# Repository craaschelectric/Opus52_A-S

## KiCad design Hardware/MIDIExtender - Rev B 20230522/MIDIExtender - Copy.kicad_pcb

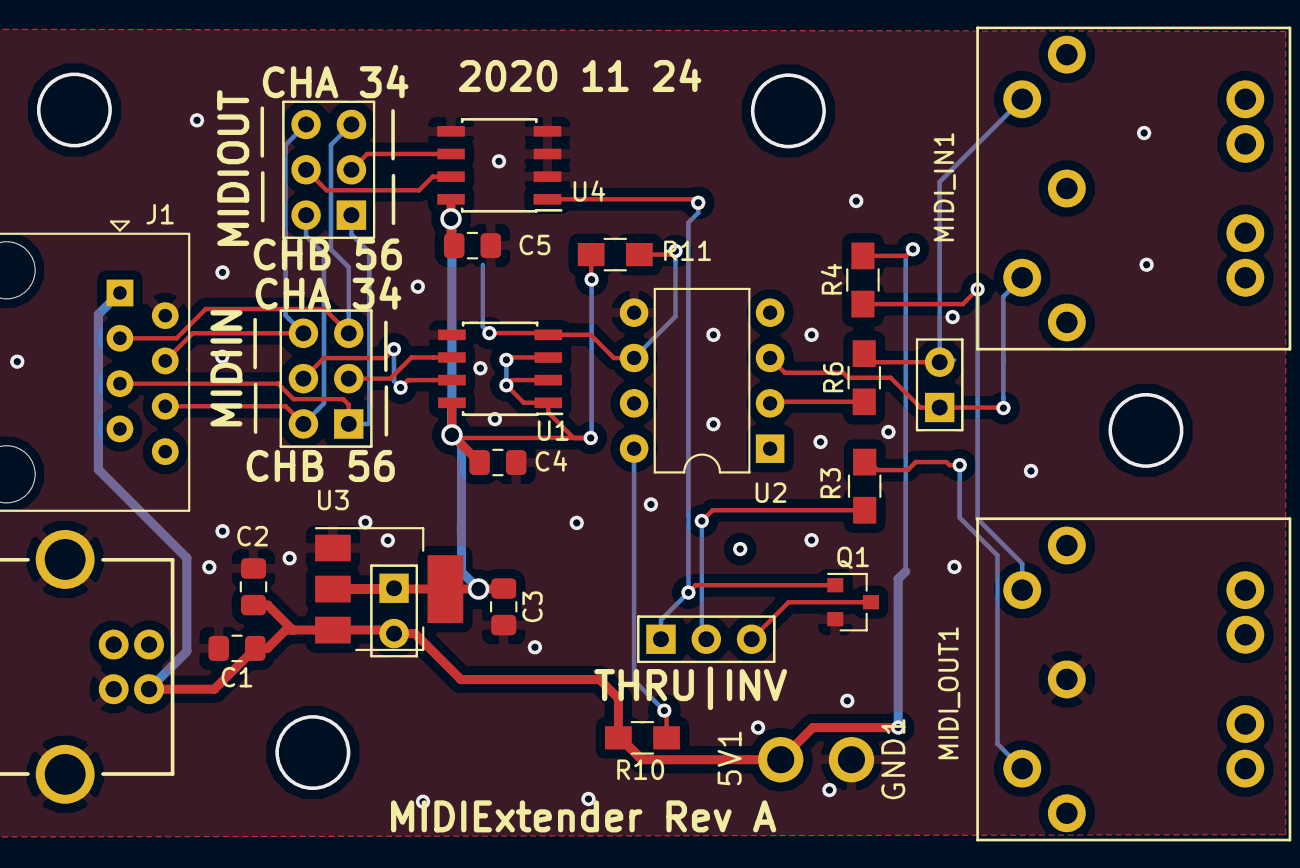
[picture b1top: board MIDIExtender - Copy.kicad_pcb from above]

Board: 2 copper layers, 26 parts (0 on the bottom side), 21 nets.

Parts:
5V1: Conn_01x01; KK156-1
C1, C2, C3, C4, C5: C; C_0805_2012Metric_Pad1.15x1.40mm_HandSolder
CHAN1, CHAN2: JBlock; H2X3-2.54
GND1: Conn_01x01; KK156-1
J1: RJ45; RJ45_Amphenol_54602-x08_Horizontal
J2, J10: Conn_01x02_Male; H2-2.54
JP1: DIP-USB-B-TYPE-FMAL_4+2P-2.0-90D_; USB4+2-2.5-90D-15.8X12MM
MIDI_IN1: DIN-5; DIN5_KCDX-5S-S2
MIDI_OUT1: DIN-5; DIN5_KCDX-5S-S2
Pol1: Conn_01x03; H3-2.54
Q1: 2N7002; SOT-23
R3, R4, R6, R11: 220; R_0805_HandSoldering
R10: 1K; R_0805_HandSoldering
U1, U4: ST485EBDR; SOIC-8_3.9x4.9mm_P1.27mm
U2: 6N138; DIP-8_W7.62mm
U3: AP1117-33; SOT-223-3_TabPin2

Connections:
/5V: 5V1.1, C1.1, C2.1, J1.1, J2.2, JP1.VBUS, R4.2, R10.2, U3.3
/MIDIIN: R11.1, U1.4, U2.6
GND: C1.2, C2.2, C3.2, C4.2, C5.2, GND1.1, J1.2, JP1.GND, JP1.S1, JP1.S2, MIDI_OUT1.3, Q1.2, U1.5, U2.5, U3.1, U4.2, U4.3, U4.4, U4.5
unnamed: C3.1, C4.1, C5.1, J2.1, R11.2, U1.1, U1.2, U1.3, U1.8, U3.2, U4.8
unnamed: CHAN1.1, CHAN2.1, J1.5
unnamed: CHAN1.2, U1.6
unnamed: CHAN1.3, CHAN2.3, J1.3
unnamed: CHAN1.4, CHAN2.4, J1.4
unnamed: CHAN1.5, U1.7
unnamed: CHAN1.6, CHAN2.6, J1.6
unnamed: CHAN2.2, U4.6
unnamed: CHAN2.5, U4.7
unnamed: J10.1, MIDI_IN1.4, U2.3
unnamed: J10.2, MIDI_IN1.2, R6.2
unnamed: MIDI_OUT1.2, R4.1
unnamed: MIDI_OUT1.4, R3.2
unnamed: Pol1.1, Q1.1, U4.1
unnamed: Pol1.2, R3.1
unnamed: Pol1.3, Q1.3
unnamed: R6.1, U2.2
unnamed: R10.1, U2.8

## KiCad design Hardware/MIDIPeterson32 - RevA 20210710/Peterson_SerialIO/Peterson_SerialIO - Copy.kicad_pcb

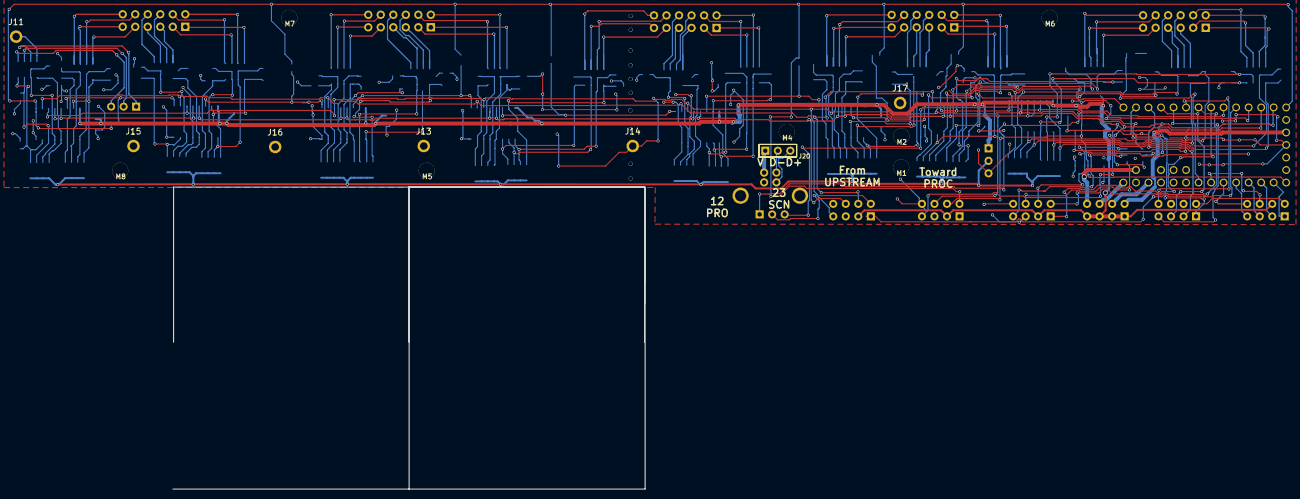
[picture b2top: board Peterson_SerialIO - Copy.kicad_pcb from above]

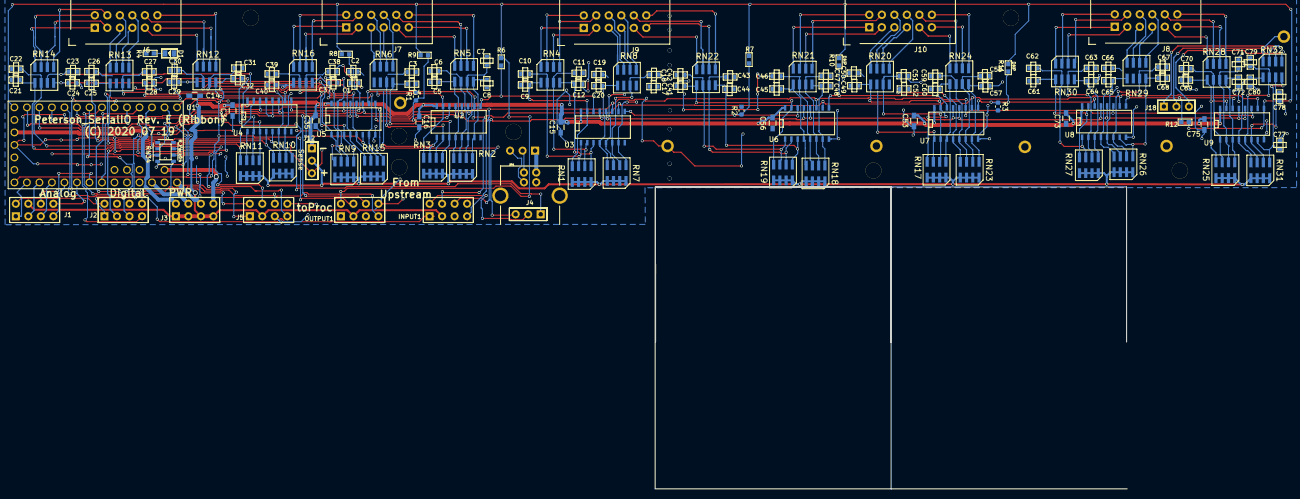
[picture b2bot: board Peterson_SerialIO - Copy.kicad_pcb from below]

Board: 2 copper layers, 156 parts (142 on the bottom side), 171 nets.

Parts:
C1, C2, C3, C4, C5, C6, C7, C8, C9, C10, C11, C12, C17, C18, C19, C20, C21, C22, C23, C24, C25, C26, C27, C28, C29, C30, C31, C32, C37, C38, C39, C40, C41, C42, C43, C44, C45, C46, C47, C48, C49, C50, C51, C52, C57, C58, C59, C60, C61, C62, C63, C64, C65, C66, C67, C68, C69, C70, C71, C72, C77, C78, C79, C80: 1nF or ESD; C0603
C14, C15, C16, C35, C36, C53, C56, C73, C75: C; R_0603_HandSoldering
D1: SMD-LED-CLEAR-GREEN_0805_; LED-0805
INPUT1: Conn_02x04_Counter_Clockwise; H2X4-2.54
J1, J2, J3, J5: Conn_02x04_Counter_Clockwise; H2X4-2.54
J4, J12, J18: Conn_01x03; H3-2.54
J6, J7, J8, J9, J10: Conn_01x12; RibbonCableSocket_12_OddEven
J11, J13, J14, J15, J16, J17: Conn_01x01; KK156-1
J20: Conn_01x03_Male; H3-2.54
JP1: DIP-USB-B-TYPE-FMAL_4+2P-2.0-90D_; USB4+2-2.5-90D-15.8X12MM
M1, M2, M4, M5, M6, M7, M8: Conn_01x01; Mounting#4
OUTPUT1: Conn_02x04_Counter_Clockwise; H2X4-2.54
R1, R2, R3: DNP; R_0603_1608Metric
R4: 1K; R0603
R6, R7, R8, R9, R10, R11, R12: DNP; R0603
RN1, RN2, RN3, RN4, RN5, RN6, RN7, RN8, RN9, RN10, RN11, RN12, RN13, RN14, RN15, RN16, RN17, RN18, RN19, RN20, RN21, RN22, RN23, RN24, RN25, RN26, RN27, RN28, RN29, RN30, RN31, RN32: R_Pack04; 2012-8
RN34: R_Pack04; RA2012-8
U1: Teensy3.2; Teensy3.x_LC
U2, U3, U4, U5, U6, U7, U8, U9: 74HC597; SO-16-N

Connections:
/ChainIn: J4.3, U1.9, U4.14
/EXT1PIN1: INPUT1.1, U1.10
/EXT1PIN8: J4.1, U1.11
/InRegLoad: INPUT1.6, OUTPUT1.6, RN34.8, U1.12, U2.12, U2.13, U3.12, U3.13, U4.12, U4.13, U5.12, U5.13, U6.12, U6.13, U7.12, U7.13, U8.12, U8.13, U9.12, U9.13
/LPWM: D1.+, U1.27
/OUT0: J6.1, RN14.8
/OUT1: J6.2, RN14.7
/OUT2: J6.3, RN14.6
/OUT3: J6.4, RN14.5
/OUT4: J6.5, RN13.8
/OUT5: J6.6, RN13.7
/OUT6: J6.7, RN13.6
/OUT7: J6.8, RN13.5
/OUT8: J6.9, RN12.8
/OUT9: J6.10, RN12.7
/OUT10: J6.11, RN12.6
/OUT11: J6.12, RN12.5
/OUT12: J7.1, RN16.8
/OUT13: J7.2, RN16.7
/OUT14: J7.3, RN16.6
/OUT15: J7.4, RN16.5
/OUT16: J7.5, RN6.8
/OUT17: J7.6, RN6.7
/OUT18: J7.7, RN6.6
/OUT19: J7.8, RN6.5
/OUT20: J7.9, RN5.8
/OUT21: J7.10, RN5.7
/OUT22: J7.11, RN5.6
/OUT23: J7.12, RN5.5
/OUT24: J9.1, RN4.8
/OUT25: J9.2, RN4.7
/OUT26: J9.3, RN4.6
/OUT27: J9.4, RN4.5
/OUT28: J9.5, RN8.8
/OUT29: J9.6, RN8.7
/OUT30: J9.7, RN8.6
/OUT31: J9.8, RN8.5
/OUT32: J9.9, RN22.8
/OUT33: J9.10, RN22.7
/OUT34: J9.11, RN22.6
/OUT35: J9.12, RN22.5
/OUT36: J10.1, RN21.8
/OUT37: J10.2, RN21.7
/OUT38: J10.3, RN21.6
/OUT39: J10.4, RN21.5
/OUT40: J10.5, RN20.8
/OUT41: J10.6, RN20.7
/OUT42: J10.7, RN20.6
/OUT43: J10.8, RN20.5
/OUT44: J10.9, RN24.8
/OUT45: J10.10, RN24.7
/OUT46: J10.11, RN24.6
/OUT47: J10.12, RN24.5
/OUT48: J8.1, RN30.8
/OUT49: J8.2, RN30.7
/OUT50: J8.3, RN30.6
/OUT51: J8.4, RN30.5
/OUT52: J8.5, RN29.8
/OUT53: J8.6, RN29.7
/OUT54: J8.7, RN29.6
/OUT55: J8.8, RN29.5
/OUT56: J8.9, RN28.8
/OUT57: J8.10, RN28.7
/OUT58: J8.11, RN28.6
/OUT59: J8.12, RN28.5
/OUT60: J11.1, RN32.8
/OUT61: J18.1, RN32.7
/OUT62: J18.2, RN32.6
/OUT63: J18.3, RN32.5
/PULLTERM: J12.2, RN1.5, RN1.6, RN1.7, RN1.8, RN2.5, RN2.6, RN2.7, RN2.8, RN3.5, RN3.6, RN3.7, RN3.8, RN7.5, RN7.6, RN7.7, RN7.8, RN9.5, RN9.6, RN9.7, RN9.8, RN10.5, RN10.6, RN10.7, RN10.8, RN11.5, RN11.6, RN11.7, RN11.8, RN15.5, RN15.6, RN15.7, RN15.8, RN17.5, RN17.6, RN17.7, RN17.8, RN18.5, RN18.6, RN18.7, RN18.8, RN19.5, RN19.6, RN19.7, RN19.8, RN23.5, RN23.6, RN23.7, RN23.8, RN25.5, RN25.6, RN25.7, RN25.8, RN26.5, RN26.6, RN26.7, RN26.8, RN27.5, RN27.6, RN27.7, RN27.8, RN31.5, RN31.6, RN31.7, RN31.8
/Ports33_48/SERIn2: R2.1, R7.2, U3.9, U6.14
/Ports49_64/SERIn3: R3.1, R11.2, U7.9, U8.14
/SEROut0: R1.1, R9.2, U2.14, U5.9
/SerialCLK: INPUT1.4, OUTPUT1.4, RN34.7, U1.13, U2.11, U3.11, U4.11, U5.11, U6.11, U7.11, U8.11, U9.11
/X2CLK: J5.4, RN34.2
/X2LOAD: J5.6, RN34.1
/X2PIN1: J5.1, U1.8
/X2PIN8: J5.8, U1.7
/X2RST: J5.7, RN34.3
/nRST: INPUT1.7, OUTPUT1.7, RN34.6, U1.20, U2.10, U3.10, U4.10, U5.10, U6.10, U7.10, U8.10, U9.10
CHAINOUT: OUTPUT1.8, R6.1, R7.1, R8.1, R9.1, R10.1, R11.1, R12.1, U1.14, U9.9
GND: C1.2, C2.2, C3.2, C4.2, C5.2, C6.2, C7.2, C8.2, C9.2, C10.2, C11.2, C12.2, C14.2, C15.2, C16.2, C17.2, C18.2, C19.2, C20.2, C21.2, C22.2, C23.2, C24.2, C25.2, C26.2, C27.2, C28.2, C29.2, C30.2, C31.2, C32.2, C35.2, C36.2, C37.2, C38.2, C39.2, C40.2, C41.2, C42.2, C43.2, C44.2, C45.2, C46.2, C47.2, C48.2, C49.2, C50.2, C51.2, C52.2, C53.2, C56.2, C57.2, C58.2, C59.2, C60.2, C61.2, C62.2, C63.2, C64.2, C65.2, C66.2, C67.2, C68.2, C69.2, C70.2, C71.2, C72.2, C73.2, C75.2, C77.2, C78.2, C79.2, C80.2, INPUT1.3, INPUT1.5, J1.8, J2.8, J5.3, J5.5, J12.3, J13.1, J14.1, J15.1, J16.1, J17.1, JP1.GND, JP1.S1, JP1.S2, OUTPUT1.3, OUTPUT1.5, R1.2, R2.2, R3.2, R4.2, U1.1, U1.17, U1.32, U2.8, U3.8, U4.8, U5.8, U6.8, U7.8, U8.8, U9.8
unnamed: C1.1, RN3.4, RN6.1, U2.15
unnamed: C2.1, RN3.3, RN6.2, U2.1
unnamed: C3.1, RN3.2, RN6.3, U2.2
unnamed: C4.1, RN3.1, RN6.4, U2.3
unnamed: C5.1, RN2.4, RN5.1, U2.4
unnamed: C6.1, RN2.3, RN5.2, U2.5
unnamed: C7.1, RN2.2, RN5.3, U2.6
unnamed: C8.1, RN2.1, RN5.4, U2.7
unnamed: C9.1, RN1.4, RN4.1, U3.15
unnamed: C10.1, RN1.3, RN4.2, U3.1
unnamed: C11.1, RN1.2, RN4.3, U3.2
unnamed: C12.1, RN1.1, RN4.4, U3.3
unnamed: C17.1, RN7.1, RN8.4, U3.7
unnamed: C18.1, RN7.2, RN8.3, U3.6
unnamed: C19.1, RN7.3, RN8.2, U3.5
unnamed: C20.1, RN7.4, RN8.1, U3.4
unnamed: C21.1, RN11.4, RN14.1, U4.15
unnamed: C22.1, RN11.3, RN14.2, U4.1
unnamed: C23.1, RN11.2, RN14.3, U4.2
unnamed: C24.1, RN11.1, RN14.4, U4.3
unnamed: C25.1, RN10.4, RN13.1, U4.4
unnamed: C26.1, RN10.3, RN13.2, U4.5
unnamed: C27.1, RN10.2, RN13.3, U4.6
unnamed: C28.1, RN10.1, RN13.4, U4.7
unnamed: C29.1, RN9.4, RN12.1, U5.15
unnamed: C30.1, RN9.3, RN12.2, U5.1
unnamed: C31.1, RN9.2, RN12.3, U5.2
unnamed: C32.1, RN9.1, RN12.4, U5.3
unnamed: C37.1, RN15.1, RN16.4, U5.7
unnamed: C38.1, RN15.2, RN16.3, U5.6
unnamed: C39.1, RN15.3, RN16.2, U5.5
unnamed: C40.1, RN15.4, RN16.1, U5.4
unnamed: C41.1, RN19.4, RN22.1, U6.15
unnamed: C42.1, RN19.3, RN22.2, U6.1
unnamed: C43.1, RN19.2, RN22.3, U6.2
unnamed: C44.1, RN19.1, RN22.4, U6.3
unnamed: C45.1, RN18.4, RN21.1, U6.4
unnamed: C46.1, RN18.3, RN21.2, U6.5
unnamed: C47.1, RN18.2, RN21.3, U6.6
unnamed: C48.1, RN18.1, RN21.4, U6.7
unnamed: C49.1, RN17.4, RN20.1, U7.15
unnamed: C50.1, RN17.3, RN20.2, U7.1
unnamed: C51.1, RN17.2, RN20.3, U7.2
unnamed: C52.1, RN17.1, RN20.4, U7.3
unnamed: C57.1, RN23.1, RN24.4, U7.7
unnamed: C58.1, RN23.2, RN24.3, U7.6
unnamed: C59.1, RN23.3, RN24.2, U7.5
unnamed: C60.1, RN23.4, RN24.1, U7.4
unnamed: C61.1, RN27.4, RN30.1, U8.15
unnamed: C62.1, RN27.3, RN30.2, U8.1
unnamed: C63.1, RN27.2, RN30.3, U8.2
unnamed: C64.1, RN27.1, RN30.4, U8.3
unnamed: C65.1, RN26.4, RN29.1, U8.4
unnamed: C66.1, RN26.3, RN29.2, U8.5
unnamed: C67.1, RN26.2, RN29.3, U8.6
unnamed: C68.1, RN26.1, RN29.4, U8.7
unnamed: C69.1, RN25.4, RN28.1, U9.15
unnamed: C70.1, RN25.3, RN28.2, U9.1
unnamed: C71.1, RN25.2, RN28.3, U9.2
unnamed: C72.1, RN25.1, RN28.4, U9.3
unnamed: C77.1, RN31.1, RN32.4, U9.7
unnamed: C78.1, RN31.2, RN32.3, U9.6
unnamed: C79.1, RN31.3, RN32.2, U9.5
unnamed: C80.1, RN31.4, RN32.1, U9.4
unnamed: D1.-, R4.1
unnamed: INPUT1.8, J4.2
unnamed: J1.1, U1.21
unnamed: J1.2, U1.22
unnamed: J1.3, U1.23
unnamed: J1.4, U1.24
unnamed: J1.5, U1.25
unnamed: J1.6, U1.26
unnamed: J2.1, U1.2
unnamed: J2.2, U1.3
unnamed: J2.3, U1.4
unnamed: J2.4, U1.5
unnamed: J2.5, U1.6
unnamed: J3.5, U1.34
unnamed: J3.6, U1.33
unnamed: J3.7, U1.31
unnamed: J3.8, U1.16
unnamed: J20.1, JP1.VBUS
unnamed: J20.2, JP1.D-
unnamed: J20.3, JP1.D+
unnamed: R6.2, U2.9, U3.14
unnamed: R8.2, U4.9, U5.14
unnamed: R10.2, U6.9, U7.14
unnamed: R12.2, U8.9, U9.14
VCC: C14.1, C15.1, C16.1, C35.1, C36.1, C53.1, C56.1, C73.1, C75.1, INPUT1.2, J1.7, J3.1, J3.2, J3.3, J3.4, J5.2, J12.1, OUTPUT1.2, U2.16, U3.16, U4.16, U5.16, U6.16, U7.16, U8.16, U9.16

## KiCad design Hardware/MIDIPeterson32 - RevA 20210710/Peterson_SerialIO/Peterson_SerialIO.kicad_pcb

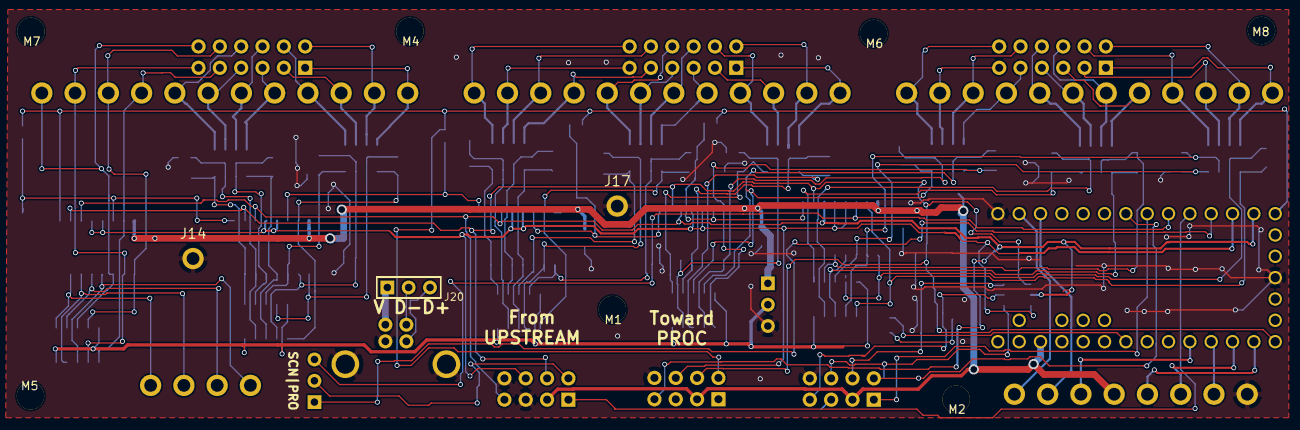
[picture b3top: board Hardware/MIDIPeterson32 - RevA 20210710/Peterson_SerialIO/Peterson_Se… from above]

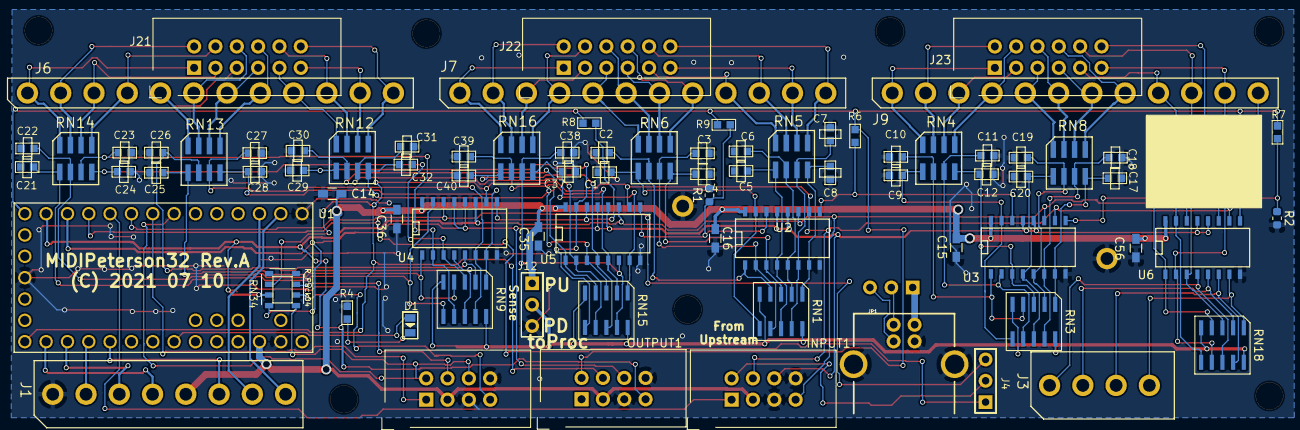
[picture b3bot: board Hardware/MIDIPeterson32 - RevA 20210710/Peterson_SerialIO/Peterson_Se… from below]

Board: 2 copper layers, 90 parts (80 on the bottom side), 103 nets.

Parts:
C1, C2, C3, C4, C5, C6, C7, C8, C9, C10, C11, C12, C17, C18, C19, C20, C21, C22, C23, C24, C25, C26, C27, C28, C29, C30, C31, C32, C37, C38, C39, C40: 1nF or ESD; C0603
C14, C15, C16, C35, C36, C56: C; R_0603_HandSoldering
D1: SMD-LED-CLEAR-GREEN_0805_; LED-0805
INPUT1: Conn_02x04_Counter_Clockwise; RibbonCableSocket_8_CCW
J1: Conn_01x08; KK156-8
J3: Conn_01x04; KK156-4
J4, J12: Conn_01x03; H3-2.54
J5: Conn_02x04_Counter_Clockwise; RibbonCableSocket_8_CCW
J6, J7, J9: Conn_01x12; KK156-12
J14, J17: Conn_01x01; KK156-1
J20: Conn_01x03_Male; H3-2.54
J21, J22, J23: Conn_01x12; RibbonCableSocket_12_OddEven
JP1: DIP-USB-B-TYPE-FMAL_4+2P-2.0-90D_; USB4+2-2.5-90D-15.8X12MM
M1, M2, M4, M5, M6, M7, M8: Conn_01x01; Mounting#4
OUTPUT1: Conn_02x04_Counter_Clockwise; RibbonCableSocket_8_CCW
R1, R2: DNP; R_0603_1608Metric
R4: 1K; R0603
R6, R7, R8, R9: DNP; R0603
RN1, RN3, RN9, RN15, RN18: R_Network08_10Pin; EXBA10P
RN4, RN5, RN6, RN8, RN12, RN13, RN14, RN16: R_Pack04; 2012-8
RN34: R_Pack04; RA2012-8
U1: Teensy3.2; Teensy3.x_LC
U2, U3, U4, U5, U6: 74HC597; SO-16-N

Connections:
/ChainIn: J4.3, U1.9, U4.14
/EXT1PIN1: INPUT1.1, U1.10
/EXT1PIN8: J4.1, U1.11
/InRegLoad: INPUT1.6, OUTPUT1.6, RN34.8, U1.12, U2.12, U2.13, U3.12, U3.13, U4.12, U4.13, U5.12, U5.13, U6.12, U6.13
/LPWM: D1.+, U1.27
/OUT0: J6.1, J21.1, RN14.8
/OUT1: J6.2, J21.2, RN14.7
/OUT2: J6.3, J21.3, RN14.6
/OUT3: J6.4, J21.4, RN14.5
/OUT4: J6.5, J21.5, RN13.8
/OUT5: J6.6, J21.6, RN13.7
/OUT6: J6.7, J21.7, RN13.6
/OUT7: J6.8, J21.8, RN13.5
/OUT8: J6.9, J21.9, RN12.8
/OUT9: J6.10, J21.10, RN12.7
/OUT10: J6.11, J21.11, RN12.6
/OUT11: J6.12, J21.12, RN12.5
/OUT12: J7.1, J22.1, RN16.8
/OUT13: J7.2, J22.2, RN16.7
/OUT14: J7.3, J22.3, RN16.6
/OUT15: J7.4, J22.4, RN16.5
/OUT16: J7.5, J22.5, RN6.8
/OUT17: J7.6, J22.6, RN6.7
/OUT18: J7.7, J22.7, RN6.6
/OUT19: J7.8, J22.8, RN6.5
/OUT20: J7.9, J22.9, RN5.8
/OUT21: J7.10, J22.10, RN5.7
/OUT22: J7.11, J22.11, RN5.6
/OUT23: J7.12, J22.12, RN5.5
/OUT24: J9.1, J23.1, RN4.8
/OUT25: J9.2, J23.2, RN4.7
/OUT26: J9.3, J23.3, RN4.6
/OUT27: J9.4, J23.4, RN4.5
/OUT28: J9.5, J23.5, RN8.8
/OUT29: J9.6, J23.6, RN8.7
/OUT30: J9.7, J23.7, RN8.6
/OUT31: J9.8, J23.8, RN8.5
/OUT32: J9.9, J23.9, RN18.6, U6.15
/OUT33: J9.10, J23.10, RN18.4, U6.1
/OUT34: J9.11, J23.11, RN18.7, U6.2
/OUT35: J9.12, J23.12, RN18.3, U6.3
/OUT36: J3.1, RN18.8, U6.4
/OUT37: J3.2, RN18.2, U6.5
/OUT38: J3.3, RN18.9, U6.6
/OUT39: J3.4, RN18.1, U6.7
/PULLTERM: J12.2, RN1.5, RN1.10, RN3.5, RN3.10, RN9.5, RN9.10, RN15.5, RN15.10, RN18.5, RN18.10
/Ports33_48/SERIn2: R2.1, R7.2, U3.9, U6.14
/RX1: J1.8, U1.2
/SEROut0: R1.1, R9.2, U2.14, U5.9
/SerialCLK: INPUT1.4, OUTPUT1.4, RN34.7, U1.13, U2.11, U3.11, U4.11, U5.11, U6.11
/TX1: J1.7, U1.3
/X2CLK: J5.4, RN34.2
/X2LOAD: J5.6, RN34.1
/X2PIN1: J5.1, U1.8
/X2PIN8: J5.8, U1.7
/X2RST: J5.7, RN34.3
/nRST: INPUT1.7, OUTPUT1.7, RN34.6, U1.20, U2.10, U3.10, U4.10, U5.10, U6.10
CHAINOUT: OUTPUT1.8, R6.1, R7.1, R8.1, R9.1, U1.14, U6.9
GND: C1.2, C2.2, C3.2, C4.2, C5.2, C6.2, C7.2, C8.2, C9.2, C10.2, C11.2, C12.2, C14.2, C15.2, C16.2, C17.2, C18.2, C19.2, C20.2, C21.2, C22.2, C23.2, C24.2, C25.2, C26.2, C27.2, C28.2, C29.2, C30.2, C31.2, C32.2, C35.2, C36.2, C37.2, C38.2, C39.2, C40.2, C56.2, INPUT1.3, INPUT1.5, J1.1, J5.3, J5.5, J12.3, J14.1, J17.1, JP1.GND, JP1.S1, JP1.S2, OUTPUT1.3, OUTPUT1.5, R1.2, R2.2, R4.2, U1.1, U1.17, U1.32, U2.8, U3.8, U4.8, U5.8, U6.8
unnamed: C1.1, RN1.6, RN6.1, U2.15
unnamed: C2.1, RN1.4, RN6.2, U2.1
unnamed: C3.1, RN1.7, RN6.3, U2.2
unnamed: C4.1, RN1.3, RN6.4, U2.3
unnamed: C5.1, RN1.8, RN5.1, U2.4
unnamed: C6.1, RN1.2, RN5.2, U2.5
unnamed: C7.1, RN1.9, RN5.3, U2.6
unnamed: C8.1, RN1.1, RN5.4, U2.7
unnamed: C9.1, RN3.6, RN4.1, U3.15
unnamed: C10.1, RN3.4, RN4.2, U3.1
unnamed: C11.1, RN3.7, RN4.3, U3.2
unnamed: C12.1, RN3.3, RN4.4, U3.3
unnamed: C17.1, RN3.1, RN8.4, U3.7
unnamed: C18.1, RN3.9, RN8.3, U3.6
unnamed: C19.1, RN3.2, RN8.2, U3.5
unnamed: C20.1, RN3.8, RN8.1, U3.4
unnamed: C21.1, RN9.6, RN14.1, U4.15
unnamed: C22.1, RN9.4, RN14.2, U4.1
unnamed: C23.1, RN9.7, RN14.3, U4.2
unnamed: C24.1, RN9.3, RN14.4, U4.3
unnamed: C25.1, RN9.8, RN13.1, U4.4
unnamed: C26.1, RN9.2, RN13.2, U4.5
unnamed: C27.1, RN9.9, RN13.3, U4.6
unnamed: C28.1, RN9.1, RN13.4, U4.7
unnamed: C29.1, RN12.1, RN15.6, U5.15
unnamed: C30.1, RN12.2, RN15.4, U5.1
unnamed: C31.1, RN12.3, RN15.7, U5.2
unnamed: C32.1, RN12.4, RN15.3, U5.3
unnamed: C37.1, RN15.1, RN16.4, U5.7
unnamed: C38.1, RN15.9, RN16.3, U5.6
unnamed: C39.1, RN15.2, RN16.2, U5.5
unnamed: C40.1, RN15.8, RN16.1, U5.4
unnamed: D1.-, R4.1
unnamed: INPUT1.8, J4.2
unnamed: J1.2, U1.23
unnamed: J1.3, U1.22
unnamed: J1.4, U1.21
unnamed: J1.6, U1.24
unnamed: J20.1, JP1.VBUS
unnamed: J20.2, JP1.D-
unnamed: J20.3, JP1.D+
unnamed: R6.2, U2.9, U3.14
unnamed: R8.2, U4.9, U5.14
VCC: C14.1, C15.1, C16.1, C35.1, C36.1, C56.1, INPUT1.2, J1.5, J5.2, J12.1, OUTPUT1.2, U1.31, U2.16, U3.16, U4.16, U5.16, U6.16

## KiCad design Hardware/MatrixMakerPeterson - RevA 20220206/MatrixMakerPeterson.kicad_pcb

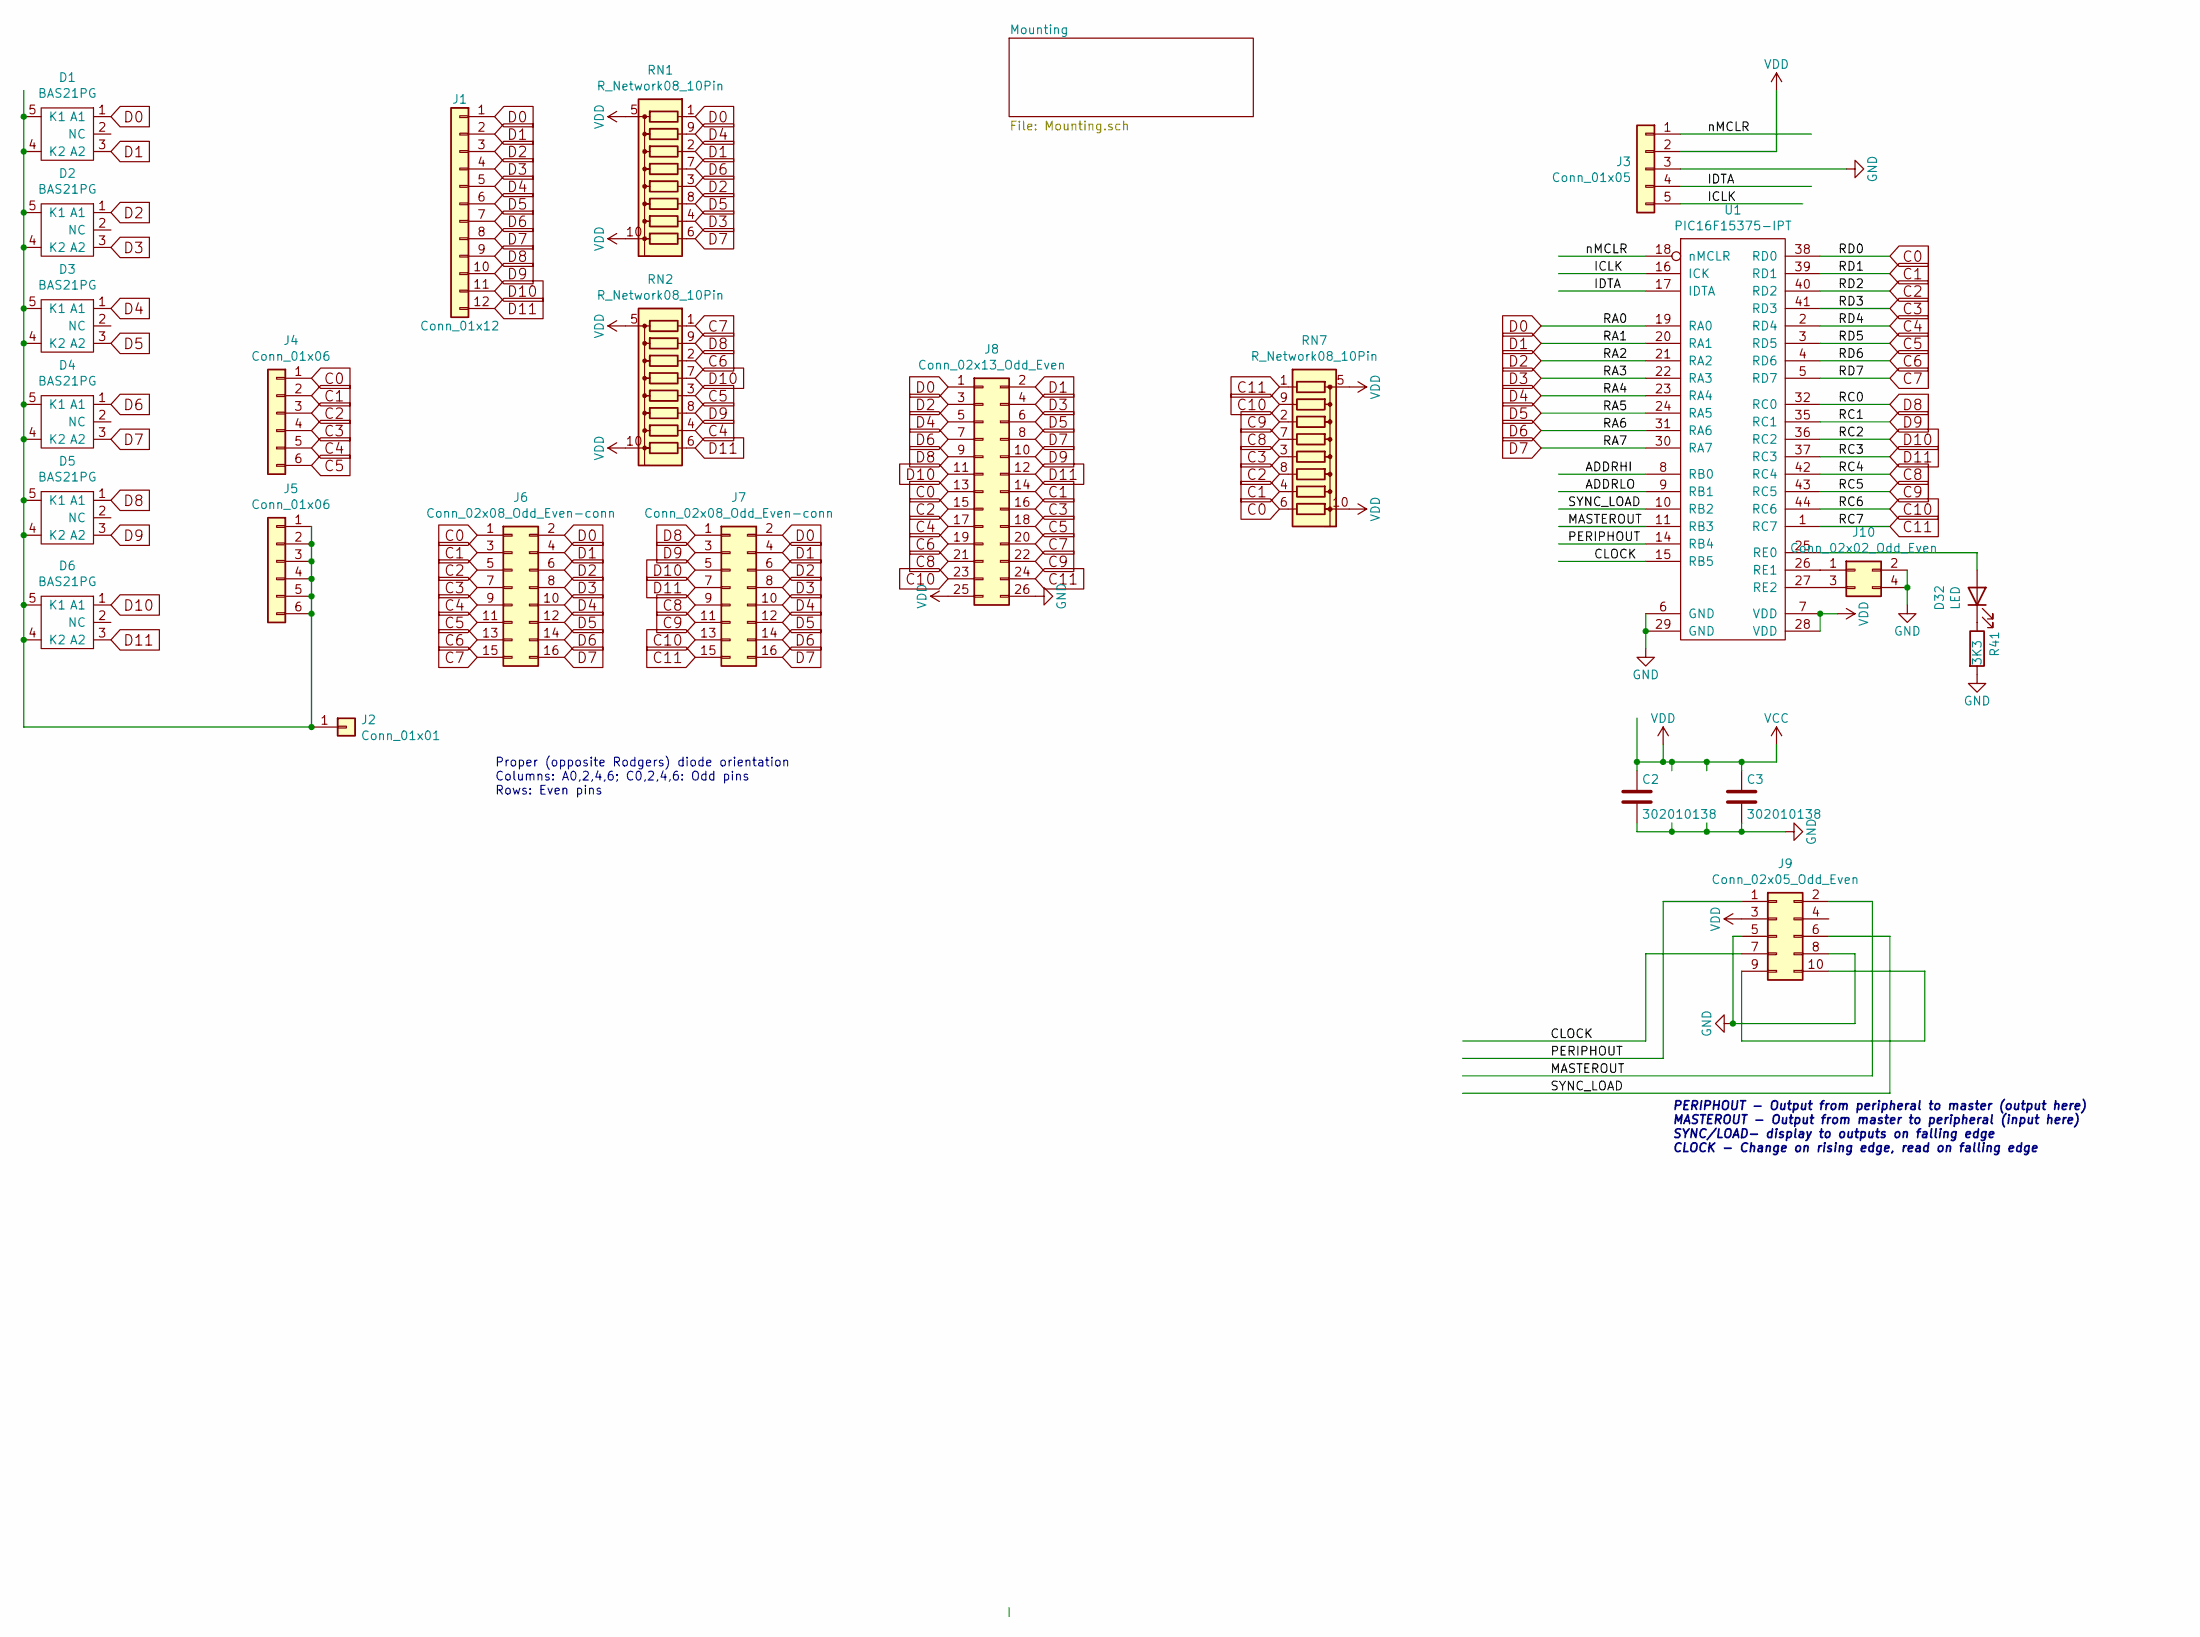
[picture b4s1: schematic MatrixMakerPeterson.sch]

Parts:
C2, C3: 302010138; C_0603_1608Metric_Pad1.08x0.95mm_HandSolder
D1, D2, D3, D4, D5, D6: BAS21PG; SOT-23-5_HandSoldering
D32: LED; LED_0805_2012Metric
J1: Conn_01x12; KK156-12
J2: Conn_01x01; KK156-1
J3: Conn_01x05; PinHeader_1x06_P2.54mm_Vertical
J4, J5: Conn_01x06; PinHeader_1x06_P2.54mm_Vertical
J6, J7: Conn_02x08_Odd_Even-conn; MicromaTch-16
J8: Conn_02x13_Odd_Even; RibbonCableSocket_26_OddEven
J9: Conn_02x05_Odd_Even; RibbonCableSocket_10_OddEven
J10: Conn_02x02_Odd_Even; PinHeader_2x02_P2.54mm_Vertical
R41: 3K3; R_0603_1608Metric_Pad0.98x0.95mm_HandSolder
RN1, RN2, RN7: R_Network08_10Pin; EXBA10P
U1: PIC16F15375-IPT; LQFP-44_10x10mm_P0.8mm

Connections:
/CLOCK: J9.7, U1.15 (RB5)
/ICLK: J3.5, U1.16 (ICK)
/IDTA: J3.4, U1.17 (IDTA)
/MASTEROUT: J9.2, U1.11 (RB3)
/PERIPHOUT: J9.1, U1.14 (RB4)
/SYNC_LOAD: J9.6, U1.10 (RB2)
/nMCLR: J3.1, U1.18 (nMCLR)
C0: J4.1, J6.1, J8.13, RN7.6 (R5), U1.38 (RD0)
C1: J4.2, J6.3, J8.14, RN7.4 (R3), U1.39 (RD1)
C2: J4.3, J6.5, J8.15, RN7.8 (R7), U1.40 (RD2)
C3: J4.4, J6.7, J8.16, RN7.3 (R2), U1.41 (RD3)
C4: J4.5, J6.9, J8.17, RN2.4 (R3), U1.2 (RD4)
C5: J4.6, J6.11, J8.18, RN2.3 (R2), U1.3 (RD5)
C6: J6.13, J8.19, RN2.2 (R1), U1.4 (RD6)
C7: J6.15, J8.20, RN2.1 (common), U1.5 (RD7)
C8: J7.9, J8.21, RN7.7 (R6), U1.42 (RC4)
C9: J7.11, J8.22, RN7.2 (R1), U1.43 (RC5)
C10: J7.13, J8.23, RN7.9 (R8), U1.44 (RC6)
C11: J7.15, J8.24, RN7.1 (common), U1.1 (RC7)
D0: D1.1 (A1), J1.1, J6.2, J7.2, J8.1, RN1.1 (common), U1.19 (RA0)
D1: D1.3 (A2), J1.2, J6.4, J7.4, J8.2, RN1.2 (R1), U1.20 (RA1)
D2: D2.1 (A1), J1.3, J6.6, J7.6, J8.3, RN1.3 (R2), U1.21 (RA2)
D3: D2.3 (A2), J1.4, J6.8, J7.8, J8.4, RN1.4 (R3), U1.22 (RA3)
D4: D3.1 (A1), J1.5, J6.10, J7.10, J8.5, RN1.9 (R8), U1.23 (RA4)
D5: D3.3 (A2), J1.6, J6.12, J7.12, J8.6, RN1.8 (R7), U1.24 (RA5)
D6: D4.1 (A1), J1.7, J6.14, J7.14, J8.7, RN1.7 (R6), U1.31 (RA6)
D7: D4.3 (A2), J1.8, J6.16, J7.16, J8.8, RN1.6 (R5), U1.30 (RA7)
D8: D5.1 (A1), J1.9, J7.1, J8.9, RN2.9 (R8), U1.32 (RC0)
D9: D5.3 (A2), J1.10, J7.3, J8.10, RN2.8 (R7), U1.35 (RC1)
D10: D6.1 (A1), J1.11, J7.5, J8.11, RN2.7 (R6), U1.36 (RC2)
D11: D6.3 (A2), J1.12, J7.7, J8.12, RN2.6 (R5), U1.37 (RC3)
GND: C2.2, C3.2, J3.3, J8.26, J9.5, J9.8, J10.2, J10.4, R41.2, U1.6 (GND), U1.29 (GND)
unnamed: D1.4 (K2), D1.5 (K1), D2.4 (K2), D2.5 (K1), D3.4 (K2), D3.5 (K1), D4.4 (K2), D4.5 (K1), D5.4 (K2), D5.5 (K1), D6.4 (K2), D6.5 (K1), J2.1, J5.1, J5.2, J5.3, J5.4, J5.5, J5.6
unnamed: D32.1 (K), R41.1
unnamed: D32.2 (A), U1.25 (RE0)
unnamed: J9.9, J9.10
unnamed: J10.1, U1.26 (RE1)
unnamed: J10.3, U1.27 (RE2)
VCC: C2.1, C3.1, J3.2, J8.25, J9.3, RN1.5 (R4), RN1.10 (R9), RN2.5 (R4), RN2.10 (R9), RN7.5 (R4), RN7.10 (R9), U1.7 (VDD), U1.28 (VDD)

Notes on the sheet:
PERIPHOUT - Output from peripheral to master (output here) MASTEROUT - Output from master to peripheral (input here) SYNC/LOAD- display to outputs on falling edge CLOCK - Change on rising edge, read on falling edge
Proper (opposite Rodgers) diode orientation Columns: A0,2,4,6; C0,2,4,6: Odd pins Rows: Even pins

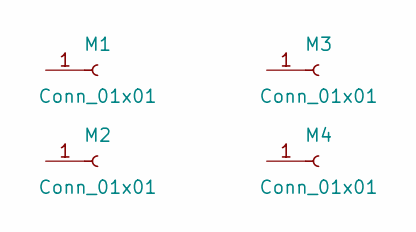
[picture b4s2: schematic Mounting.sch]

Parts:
M1, M2, M3, M4: Conn_01x01; Mounting#4

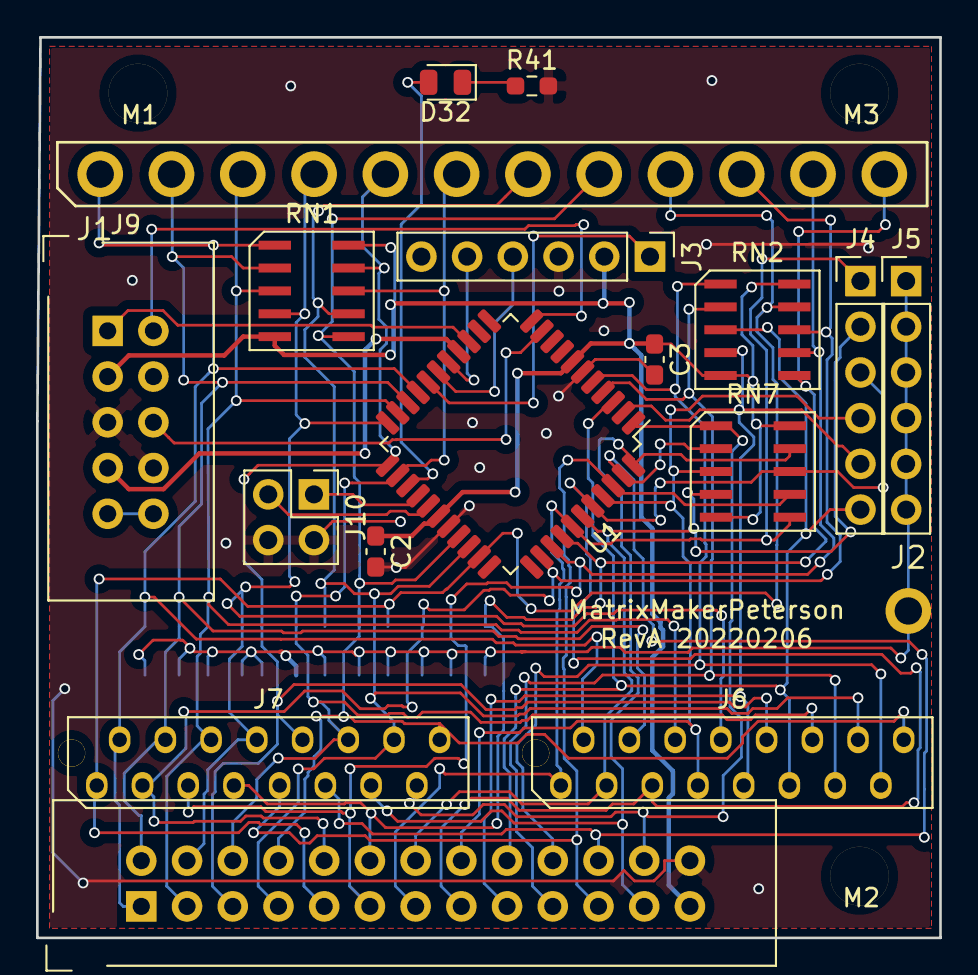
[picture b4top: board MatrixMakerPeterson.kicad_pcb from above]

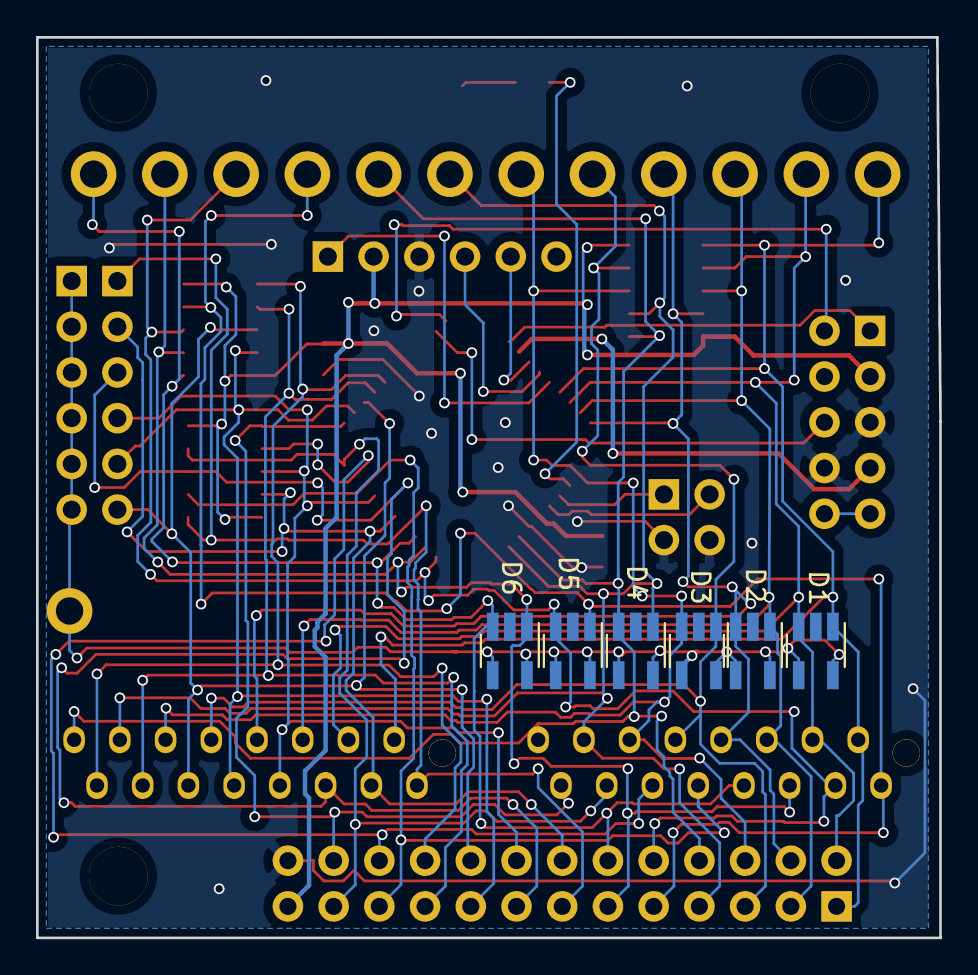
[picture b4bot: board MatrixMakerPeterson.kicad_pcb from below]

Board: 2 copper layers, 50.2 x 50.0 mm, 27 parts (6 on the bottom side), 39 nets.

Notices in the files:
Hardware/MIDIPeterson32 - RevA 20210710/Peterson_SerialIO/Peterson_SerialIO - Copy.kicad_pcb:
(C) 2020 07 19
Hardware/MIDIPeterson32 - RevA 20210710/Peterson_SerialIO/Peterson_SerialIO.kicad_pcb:
(C) 2021 07 10
Hardware/Peterson32WithAudio - RevA 20220929/Peterson_SerialIO/Peterson_SerialIO.kicad_pcb:
(C) 2022 09 26
